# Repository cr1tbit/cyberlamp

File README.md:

# Cyberlamp

An experiment about creating a tetrachromatic lamp, including infrared and ultraviolet light sources.

The LEDs are driven by ICs designed to control columns on hub75 matrices. Each LED can be toggled separately.

The onboard mcu CH582 can do bluetooth, so the lamps could be remotely controlled, atleast in theory.

In practice, i should've used PWM-enabled pin for `output enable` pin. Software PWM is glitchy, and becomes
unusable when handling bluetooth at the same time.

Next revision will most likely just use some dedicated LED drivers, and their PWM
will be controlled by dedicated PWM pin(s).

## Interface

The lamp is dedicated to work with [i2current](https://github.com/cr1tbit/i2current),
so it becomes fully battery powered. USB, power and I2C are routed through the 
side walls via stripped down CAT5 differential pairs. Voltage drop is not an issue,
I actually had to modify the powerboard to deliver ~4.2V - because the drivers would
not respond to 3.3v logic signals when powered by 5V.

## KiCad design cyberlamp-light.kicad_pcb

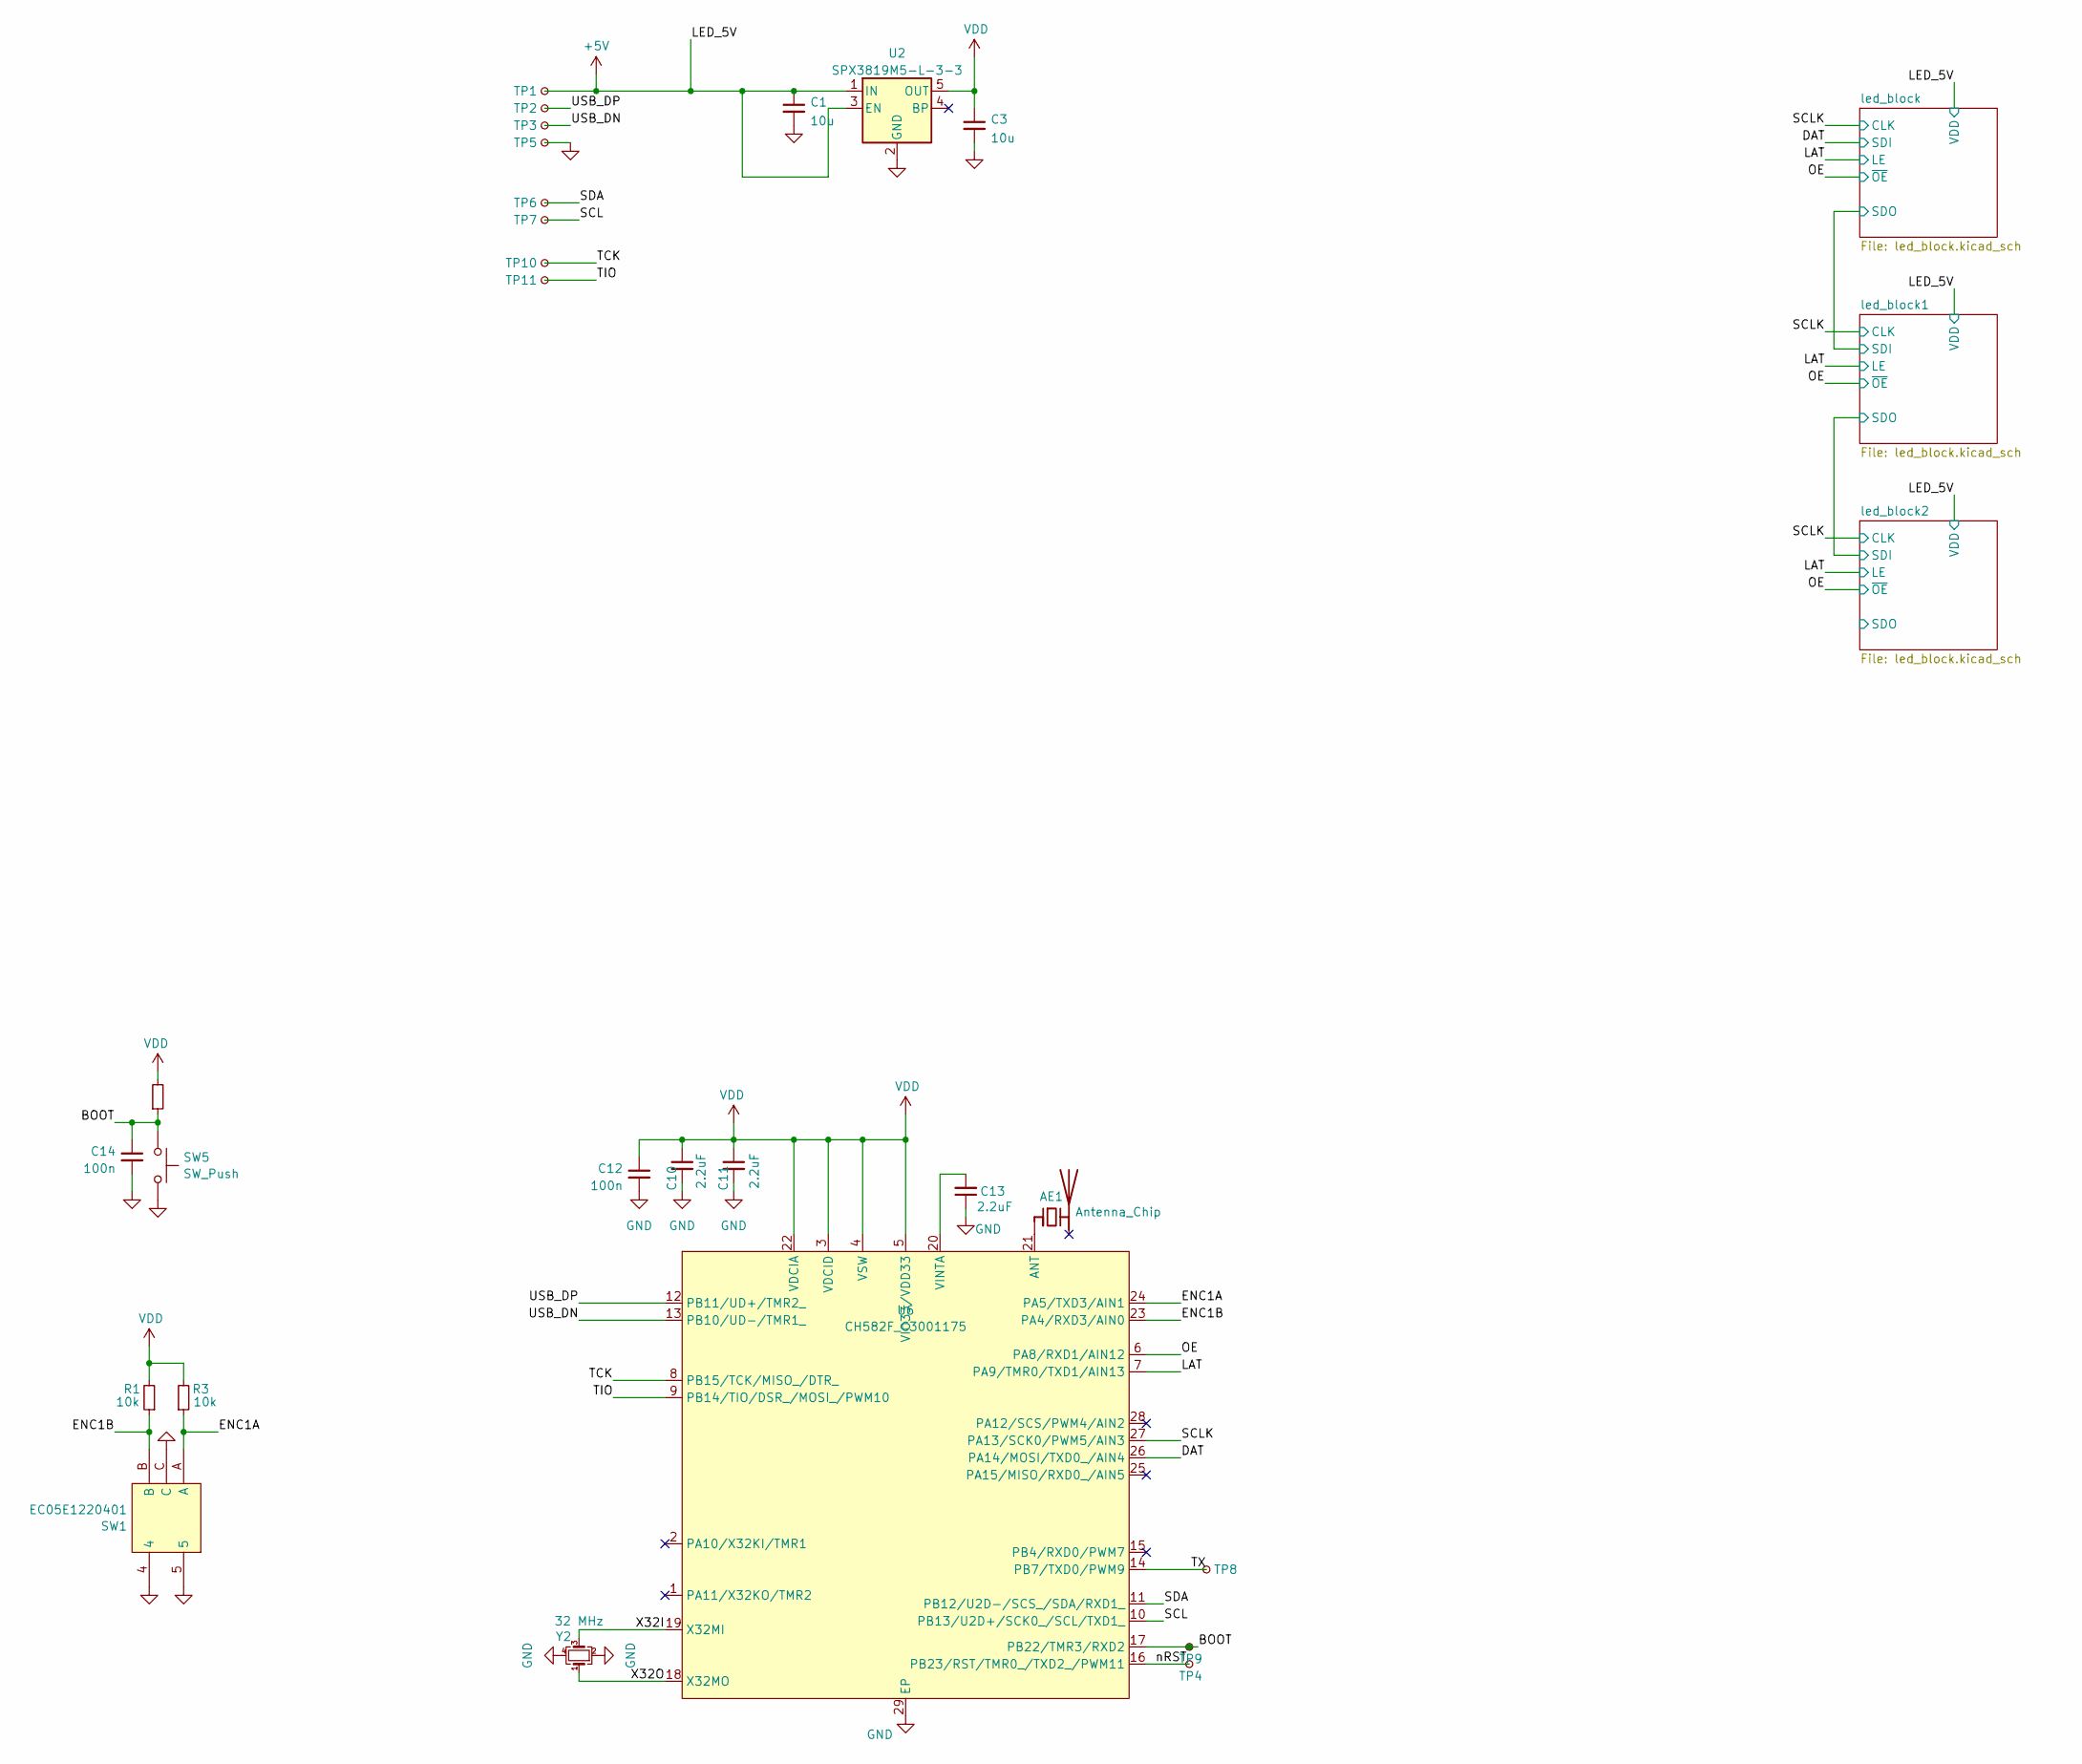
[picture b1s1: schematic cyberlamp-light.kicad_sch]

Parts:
AE1: Antenna_Chip; Johanson_2450AT18x100; LCSC C127629
C1, C3: 10u; C_0603_1608Metric; LCSC C96446
C10, C11, C13: 2.2uF; C_0402_1005Metric; LCSC C12530
C12, C14: 100n; C_0402_1005Metric; LCSC C307331
R1, R3, R13: 10k; R_0402_1005Metric; LCSC C25744
SW1: EC05E1220401; SW-SMD_EC05E1220401; LCSC C116648
SW5: SW_Push; SW_PUSH_6mm_H5mm
TP1, TP2, TP3, TP4, TP5, TP6, TP7, TP8, TP9, TP10, TP11: RX; TestPoint_Pad_D1.0mm
U2: SPX3819M5-L-3-3; SOT-23-5; LCSC C5370980
U6: CH582F_C3001175; QFN-28_L4.0-W4.0-P0.40-BL-EP2.8; LCSC C3001175
Y2: 32 MHz; Crystal_SMD_2016-4Pin_2.0x1.6mm; LCSC C2682773

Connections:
+5V: C1.1, TP1.1 (1_1), U2.1 (IN), U2.3 (EN); also elsewhere on the board
/BOOT: C14.1, R13.1, SW5.1, TP9.1 (1_1), U6.17 (PB22/TMR3/RXD2)
/DAT: U6.26 (PA14/MOSI/TXD0_/AIN4); also elsewhere on the board
/ENC1A: R3.1, SW1.A, U6.24 (PA5/TXD3/AIN1)
/ENC1B: R1.1, SW1.B, U6.23 (PA4/RXD3/AIN0)
/LAT: U6.7 (PA9/TMR0/TXD1/AIN13); also elsewhere on the board
/OE: U6.6 (PA8/RXD1/AIN12); also elsewhere on the board
/SCL: TP7.1 (1_1), U6.10 (PB13/U2D+/SCK0_/SCL/TXD1_)
/SCLK: U6.27 (PA13/SCK0/PWM5/AIN3); also elsewhere on the board
/SDA: TP6.1 (1_1), U6.11 (PB12/U2D-/SCS_/SDA/RXD1_)
/TCK: TP10.1 (1_1), U6.8 (PB15/TCK/MISO_/DTR_)
/TIO: TP11.1 (1_1), U6.9 (PB14/TIO/DSR_/MOSI_/PWM10)
/TX: TP8.1 (1_1), U6.14 (PB7/TXD0/PWM9)
/USB_DN: TP3.1 (1_1), U6.13 (PB10/UD-/TMR1_)
/USB_DP: TP2.1 (1_1), U6.12 (PB11/UD+/TMR2_)
/X32I: U6.19 (X32MI), Y2.3
/X32O: U6.18 (X32MO), Y2.1
/nRST: TP4.1 (1_1), U6.16 (PB23/RST/TMR0_/TXD2_/PWM11)
GND: C1.2, C3.2, C10.2, C11.2, C12.2, C13.1, C14.2, SW1.4, SW1.5, SW1.C, SW5.2, TP5.1 (1_1), U2.2 (GND), U6.29 (EP), Y2.2, Y2.4; also elsewhere on the board
unnamed: AE1.1 (FEED_1), U6.21 (ANT)
unnamed: C13.2, U6.20 (VINTA)
VDD: C3.1, C10.1, C11.1, C12.1, R1.2, R3.2, R13.2, U2.5 (OUT), U6.3 (VDCID), U6.4 (VSW), U6.5 (VIO33/VDD33), U6.22 (VDCIA)

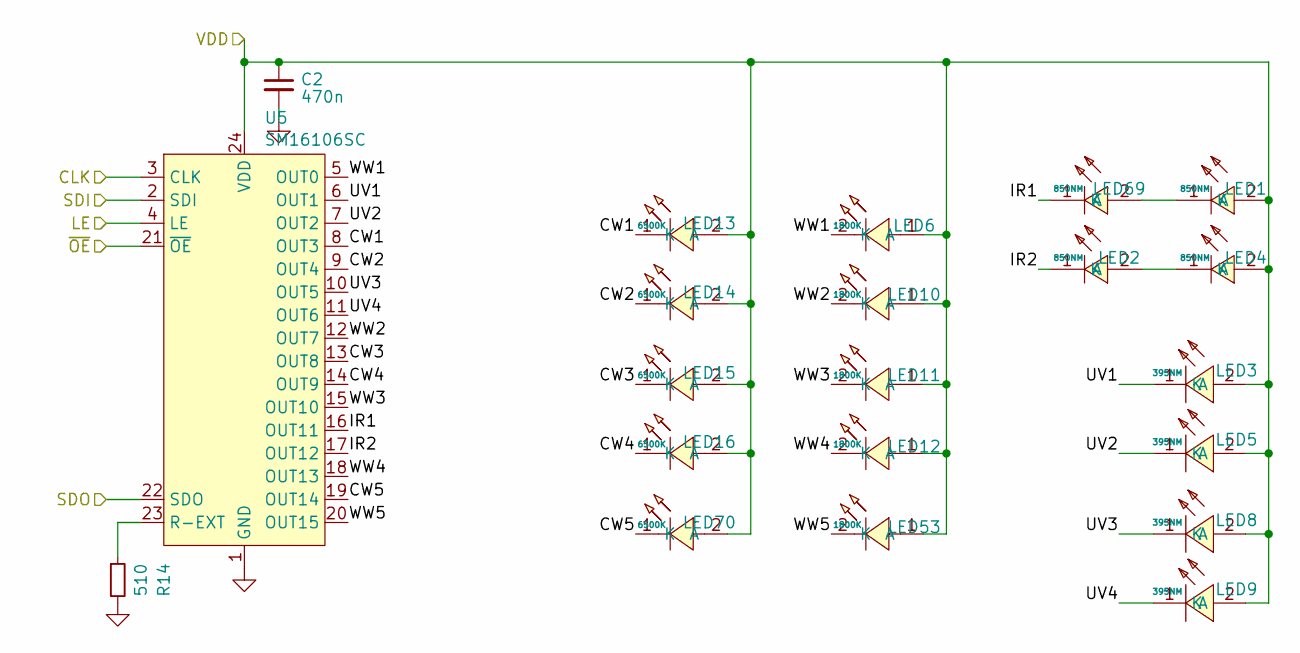
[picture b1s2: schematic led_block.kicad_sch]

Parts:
C2: 470n; C_0402_1005Metric; LCSC C52923
LED1, LED2, LED4, LED69: 850NM; LED-SMD_L3.5-W2.8_C9900017434; LCSC C5221242
LED3, LED5, LED8, LED9: 395NM; LED-SMD_L3.5-W2.8-RD_PURPLE; LCSC C2827317
LED6, LED10, LED11, LED12, LED53: 1800K; LED-SMD_L3.5-W2.8-R-RD_TJ-S2835UG5W8TLC6B-A5; LCSC C7371920
LED13, LED14, LED15, LED16, LED70: 6500K; LED-SMD_L3.5-W2.8-FD-2835_WHITE; LCSC C7423447
R14: 510; R_0402_1005Metric; LCSC C25123
U5: SM16106SC; QSOP-24_L8.7-W4.0-P0.64-LS6.0-BL; LCSC C121618

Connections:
+5V: C2.1, LED1.2 (A), LED3.2 (A), LED4.2 (A), LED5.2 (A), LED6.1 (A), LED8.2 (A), LED9.2 (A), LED10.1 (A), LED11.1 (A), LED12.1 (A), LED13.2 (A), LED14.2 (A), LED15.2 (A), LED16.2 (A), LED53.1 (A), LED70.2 (A), U5.24 (VDD); also elsewhere on the board
/DAT: U5.2 (SDI); also elsewhere on the board
/LAT: U5.4 (LE); also elsewhere on the board
/OE: U5.21 (~OE); also elsewhere on the board
/SCLK: U5.3 (CLK); also elsewhere on the board
/led_block/CW1: LED13.1 (K), U5.8 (OUT3)
/led_block/CW2: LED14.1 (K), U5.9 (OUT4)
/led_block/CW3: LED15.1 (K), U5.13 (OUT8)
/led_block/CW4: LED16.1 (K), U5.14 (OUT9)
/led_block/CW5: LED70.1 (K), U5.19 (OUT14)
/led_block/IR1: LED69.1 (K), U5.16 (OUT11)
/led_block/IR2: LED2.1 (K), U5.17 (OUT12)
/led_block/SDO: U5.22 (SDO); also elsewhere on the board
/led_block/UV1: LED3.1 (K), U5.6 (OUT1)
/led_block/UV2: LED5.1 (K), U5.7 (OUT2)
/led_block/UV3: LED8.1 (K), U5.10 (OUT5)
/led_block/UV4: LED9.1 (K), U5.11 (OUT6)
/led_block/WW1: LED6.2 (K), U5.5 (OUT0)
/led_block/WW2: LED10.2 (K), U5.12 (OUT7)
/led_block/WW3: LED11.2 (K), U5.15 (OUT10)
/led_block/WW4: LED12.2 (K), U5.18 (OUT13)
/led_block/WW5: LED53.2 (K), U5.20 (OUT15)
GND: C2.2, R14.2, U5.1 (GND); also elsewhere on the board
unnamed: LED1.1 (K), LED69.2 (A)
unnamed: LED2.2 (A), LED4.1 (K)
unnamed: R14.1, U5.23 (R-EXT)

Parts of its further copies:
C7, C8: 470n; C_0402_1005Metric; LCSC C52923
LED17, LED18, LED20, LED21, LED35, LED36, LED38, LED39: 850NM; LED-SMD_L3.5-W2.8_C9900017434; LCSC C5221242
LED19, LED22, LED24, LED27, LED30, LED37, LED40, LED42, LED45, LED48: 6500K; LED-SMD_L3.5-W2.8-FD-2835_WHITE; LCSC C7423447
LED23, LED26, LED29, LED32, LED41, LED44, LED47, LED50: 395NM; LED-SMD_L3.5-W2.8-RD_PURPLE; LCSC C2827317
LED25, LED28, LED31, LED34, LED43, LED46, LED49, LED52, LED54, LED55: 1800K; LED-SMD_L3.5-W2.8-R-RD_TJ-S2835UG5W8TLC6B-A5; LCSC C7371920
R4, R5: 510; R_0402_1005Metric; LCSC C25123
U1, U3: SM16106SC; QSOP-24_L8.7-W4.0-P0.64-LS6.0-BL; LCSC C121618

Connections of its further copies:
+5V: C7.1, C8.1, LED18.2 (A), LED19.2 (A), LED21.2 (A), LED22.2 (A), LED23.2 (A), LED24.2 (A), LED25.1 (A), LED26.2 (A), LED27.2 (A), LED28.1 (A), LED29.2 (A), LED30.2 (A), LED31.1 (A), LED32.2 (A), LED34.1 (A), LED36.2 (A), LED37.2 (A), LED39.2 (A), LED40.2 (A), LED41.2 (A), LED42.2 (A), LED43.1 (A), LED44.2 (A), LED45.2 (A), LED46.1 (A), LED47.2 (A), LED48.2 (A), LED49.1 (A), LED50.2 (A), LED52.1 (A), LED54.1 (A), LED55.1 (A), U1.24 (VDD), U3.24 (VDD); also elsewhere on the board
/LAT: U1.4 (LE), U3.4 (LE); also elsewhere on the board
/OE: U1.21 (~OE), U3.21 (~OE); also elsewhere on the board
/SCLK: U1.3 (CLK), U3.3 (CLK); also elsewhere on the board
/led_block1/CW1: LED19.1 (K), U1.8 (OUT3)
/led_block1/CW2: LED22.1 (K), U1.9 (OUT4)
/led_block1/CW3: LED24.1 (K), U1.13 (OUT8)
/led_block1/CW4: LED27.1 (K), U1.14 (OUT9)
/led_block1/CW5: LED30.1 (K), U1.19 (OUT14)
/led_block1/IR1: LED17.1 (K), U1.16 (OUT11)
/led_block1/IR2: LED20.1 (K), U1.17 (OUT12)
/led_block1/SDO: U1.22 (SDO), U3.2 (SDI)
/led_block1/UV1: LED23.1 (K), U1.6 (OUT1)
/led_block1/UV2: LED26.1 (K), U1.7 (OUT2)
/led_block1/UV3: LED29.1 (K), U1.10 (OUT5)
/led_block1/UV4: LED32.1 (K), U1.11 (OUT6)
/led_block1/WW1: LED25.2 (K), U1.5 (OUT0)
/led_block1/WW2: LED28.2 (K), U1.12 (OUT7)
/led_block1/WW3: LED31.2 (K), U1.15 (OUT10)
/led_block1/WW4: LED34.2 (K), U1.18 (OUT13)
/led_block1/WW5: LED54.2 (K), U1.20 (OUT15)
/led_block2/CW1: LED37.1 (K), U3.8 (OUT3)
/led_block2/CW2: LED40.1 (K), U3.9 (OUT4)
/led_block2/CW3: LED42.1 (K), U3.13 (OUT8)
/led_block2/CW4: LED45.1 (K), U3.14 (OUT9)
/led_block2/CW5: LED48.1 (K), U3.19 (OUT14)
/led_block2/IR1: LED35.1 (K), U3.16 (OUT11)
/led_block2/IR2: LED38.1 (K), U3.17 (OUT12)
/led_block2/SDO: U3.22 (SDO)
/led_block2/UV1: LED41.1 (K), U3.6 (OUT1)
/led_block2/UV2: LED44.1 (K), U3.7 (OUT2)
/led_block2/UV3: LED47.1 (K), U3.10 (OUT5)
/led_block2/UV4: LED50.1 (K), U3.11 (OUT6)
/led_block2/WW1: LED43.2 (K), U3.5 (OUT0)
/led_block2/WW2: LED46.2 (K), U3.12 (OUT7)
/led_block2/WW3: LED49.2 (K), U3.15 (OUT10)
/led_block2/WW4: LED52.2 (K), U3.18 (OUT13)
/led_block2/WW5: LED55.2 (K), U3.20 (OUT15)
/led_block/SDO: U1.2 (SDI); also elsewhere on the board
GND: C7.2, C8.2, R4.2, R5.2, U1.1 (GND), U3.1 (GND); also elsewhere on the board
unnamed: LED17.2 (A), LED18.1 (K)
unnamed: LED20.2 (A), LED21.1 (K)
unnamed: LED35.2 (A), LED36.1 (K)
unnamed: LED38.2 (A), LED39.1 (K)
unnamed: R4.1, U1.23 (R-EXT)
unnamed: R5.1, U3.23 (R-EXT)

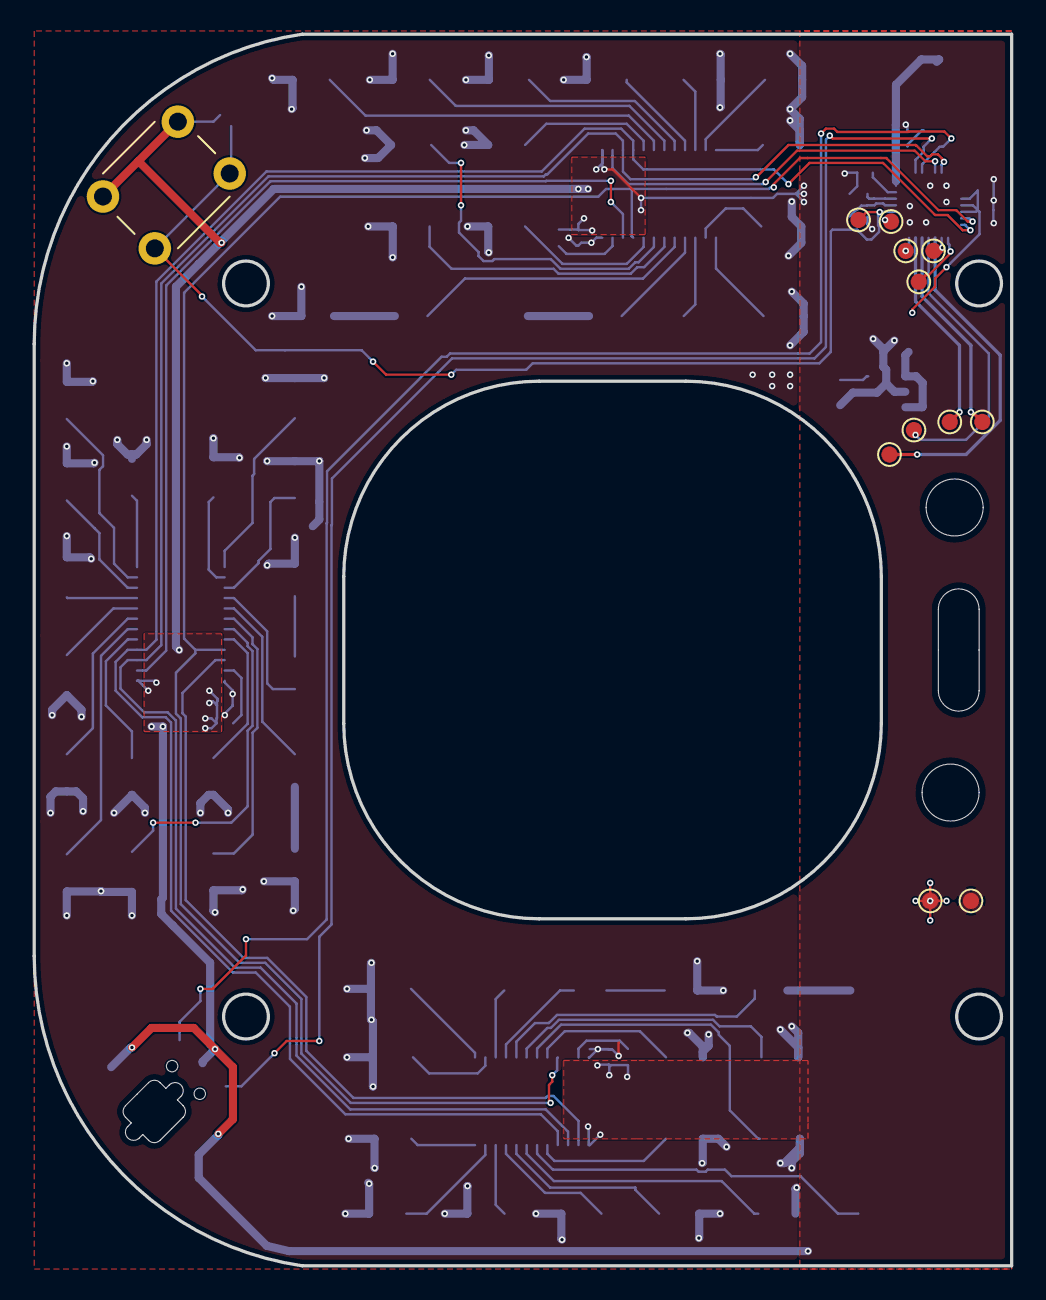
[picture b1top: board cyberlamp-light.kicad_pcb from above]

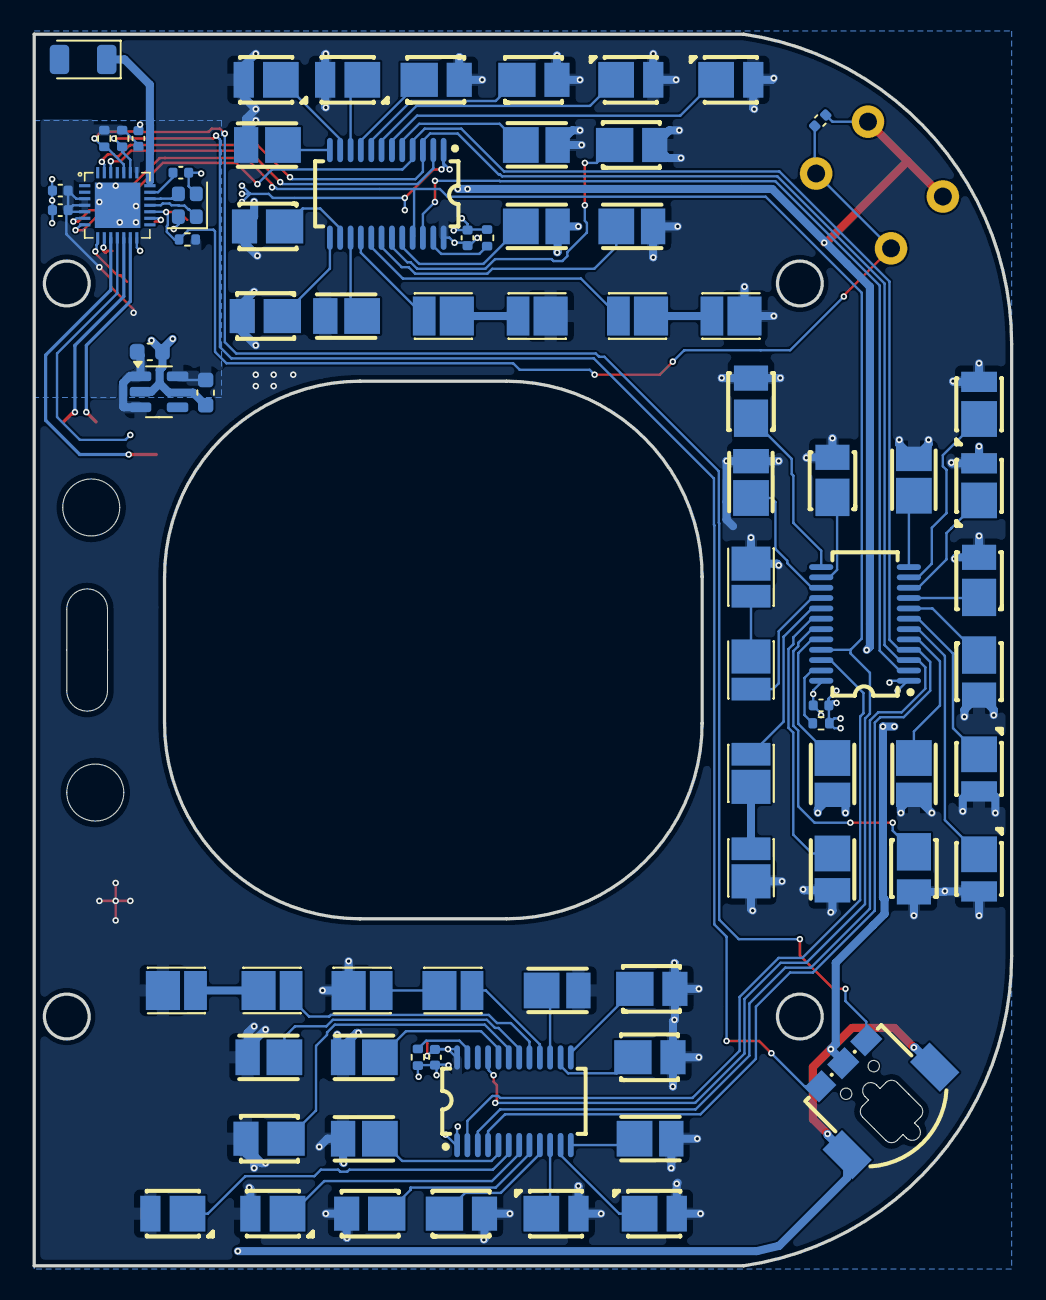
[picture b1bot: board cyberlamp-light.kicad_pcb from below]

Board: 2 copper layers, 60.0 x 75.6 mm, 90 parts (78 on the bottom side), 81 nets.

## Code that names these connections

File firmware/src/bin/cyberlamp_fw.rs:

//! Cyberlamp firmware with the BLE console (Nordic UART Service).

#![feature(impl_trait_in_assoc_type)]
#![feature(type_alias_impl_trait)]
#![feature(generic_const_exprs)]
#![no_std]
#![no_main]

use ch58x_hal as hal;
use embassy_executor::Spawner;
use hal::uart::UartTx;
use hal::ble;
use ch58x_rs_kit::ble_periph::current_time_service::current_time_init;
use ch58x_rs_kit::ble_periph::{common_init_named, devinfo_init, nus, peripheral_keep_running};
use ch58x_rs_kit::logger::init as init_logger;
use ch58x_rs_kit::sr_led_driver::SrLedDriver;
use ch58x_rs_kit::{get_configured_rtc, log, tmos_mainloop};
use cyberlamp_rs::lamp::{lamp_task, leds_off, nus_console, LED_COUNT};


#[qingke_rt::entry]
fn main() -> ! {
    hal::embassy::Executor::new().run(|spawner| spawner.must_spawn(app_main(spawner)))
}

#[qingke_rt::interrupt]
fn Exception() {
    ch58x_rs_kit::fatal::halt(core::format_args!("CPU exception"))
}

#[embassy_executor::task]
async fn app_main(spawner: Spawner) -> ! {
    let mut config = hal::Config::default();
    config.clock.use_pll_60mhz();
    let p = hal::init(config);
    ch58x_rs_kit::fatal::set_safe_state_hook(leds_off);
    hal::embassy::init();

    let serial = UartTx::new(p.UART0, p.PB7, Default::default()).unwrap();
    init_logger(serial);
    log!("\n\n\nCyberlamp Firmware Started!");

    // Cyberlamp-light SM16106SC chain:
    // SCLK - PA13, DAT - PA14, /OE - PA8, LAT - PA9.
    let sr_driver =
        SrLedDriver::<_, LED_COUNT>::new_from_pins::<false, _, _, _, _>(p.SPI0, p.PA13, p.PA14, p.PA8, p.PA9);

    log!("Shift register LED driver initialized");
    log!("  SPI: SCLK=PA13, DAT=PA14");
    log!("  GPIO: OE=PA8, LAT=PA9");

    // Timer::after(Duration::from_secs(1)).await;

    // sr_driver.test_write(0xFF);
    // sr_driver.test_write(0x00);
    log!("Starting lamp task...");

    spawner
        .spawn(lamp_task(sr_driver, p.PA5, p.PA4, p.PB22))
        .unwrap();

    let rtc = get_configured_rtc();

    log!("System Clocks: {}", hal::sysctl::clocks().hclk);
    log!("ChipID: 0x{:02x}", hal::signature::get_chip_id());
    log!("RTC datetime: {}", rtc.now());
    let lsi_hz = hal::ble::calibrate_lsi()
        .expect("BLE needs a calibrated 32000 Hz internal clock");
    log!("BLE LSI calibrated: {} Hz", lsi_hz);

    log!("BLE Lib Version: {}", ble::lib_version());

    let mut ble_config = ble::Config::default();
    ble_config.pa_config = None;
    ble_config.mac_addr = [0x21, 0x37, 0x04, 0x20, 0x69, 0x96].into();
    let (task_id, sub) = hal::ble::init(ble_config).unwrap();
    log!("BLE hal task id: {}", task_id);

    unsafe {
        common_init_named("cyberlamp");
        use hal::ble::ffi::*;
        use hal::ble::gap::GAPRole_SetParameter;
        // Automatic 2M PHY negotiation establishes a link but stalls ATT on this board.
        // Keep 1M until that path has been investigated separately.
        let phy = GAP_PHY_BIT_LE_1M as u8;
        GAPRole_SetParameter(GAPROLE_PHY_TX_SUPPORTED, 1, &phy as *const _ as _).unwrap();
        GAPRole_SetParameter(GAPROLE_PHY_RX_SUPPORTED, 1, &phy as *const _ as _).unwrap();
        devinfo_init();
        current_time_init();
        nus::init();
    }

    spawner.spawn(tmos_mainloop()).unwrap();
    spawner.spawn(nus_console()).unwrap();

    peripheral_keep_running(spawner, task_id, sub, rtc).await
}
